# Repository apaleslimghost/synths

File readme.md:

<h1 align="center">
	
</h1>

schematics, PCBs, designs and code for Pale Slim Ghost Synthesisers hardware. these can be viewed on [CADLAB.io](https://cadlab.io/project/26113).

## todo

- [ ] generate build guides with [`pcbdraw populate`](https://github.com/yaqwsx/PcbDraw/blob/master/doc/populate.md)
- [ ] publishing to github pages
- [ ] makefiles with [`kikit`](https://github.com/yaqwsx/KiKit)

## licence

unless otherwise specified:

- hardware is licenced under [CERN-OHL-S](licence-hardware.txt)
- software/firmware is licenced under [Parity Public Licence 7.0.0](licence.md)
- artwork is licenced under [Creative Commons BY-NC-SA 4.0](https://creativecommons.org/licenses/by-nc-sa/4.0/)

generally, that means you can use, edit, and make things in this repository, but please share the source if you do.

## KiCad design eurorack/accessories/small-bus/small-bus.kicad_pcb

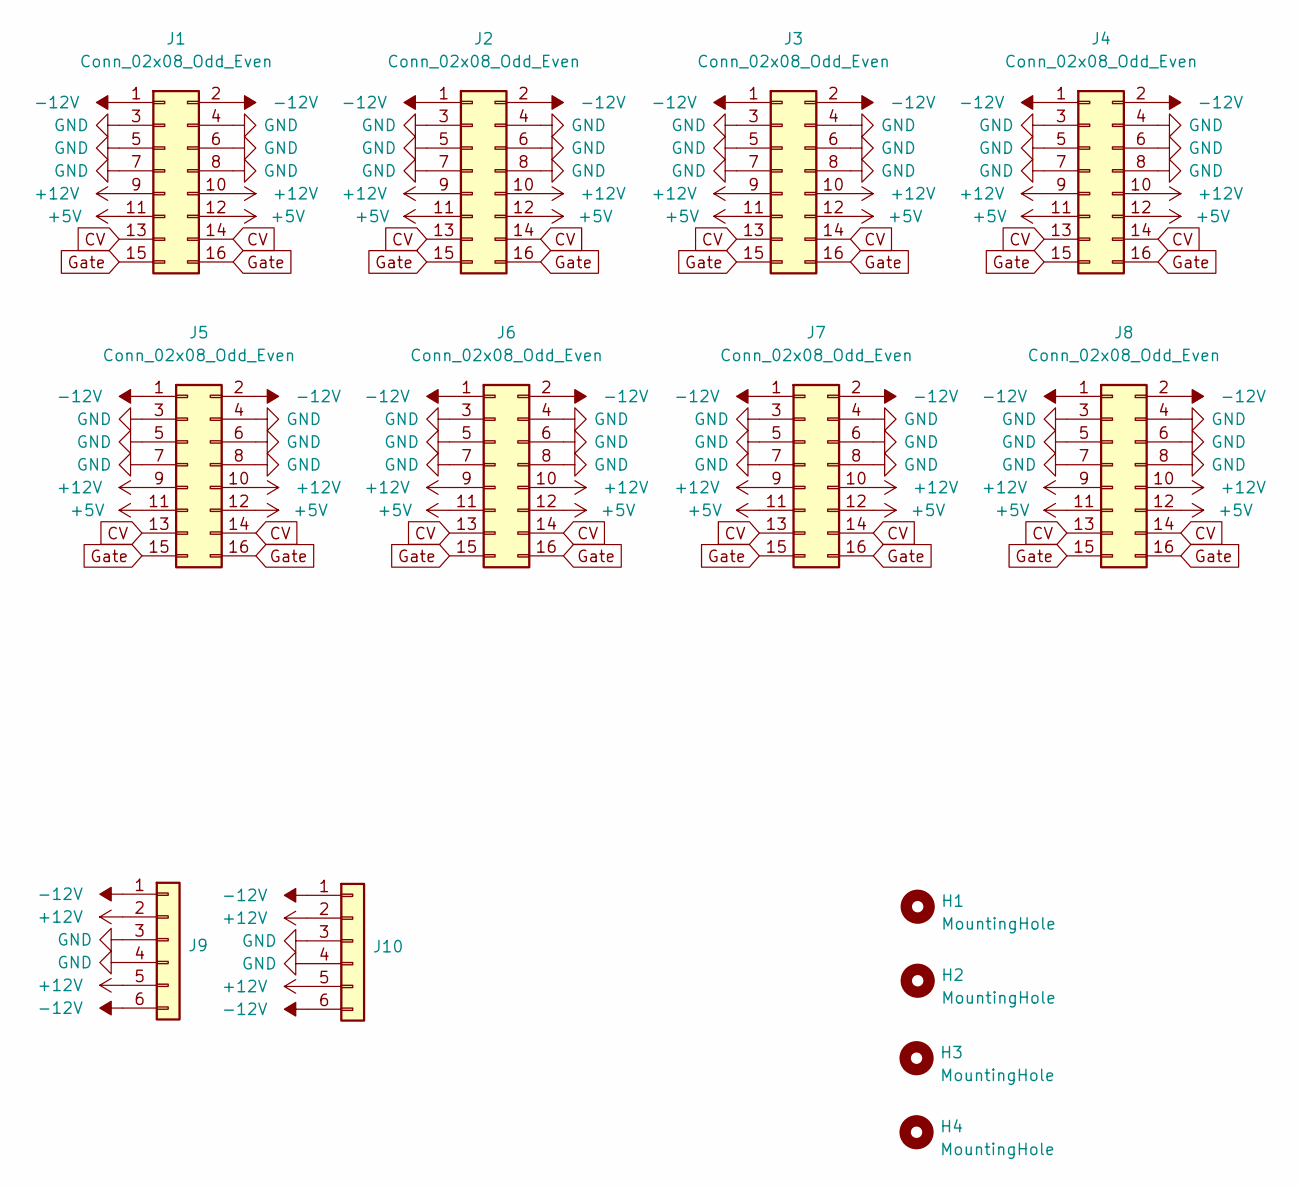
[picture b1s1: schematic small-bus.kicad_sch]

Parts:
H1, H2, H3, H4: MountingHole; MountingHole_3.2mm_M3
J1, J2, J3, J4, J5, J6, J7, J8: Conn_02x08_Odd_Even; PinHeader_2x08_P2.54mm_Edge
J9, J10: Conn_01x06; Molex_KK-254_AE-6410-06A_1x06_P2.54mm_Horizontal

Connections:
+5V: J1.11, J1.12, J2.11, J2.12, J3.11, J3.12, J4.11, J4.12, J5.11, J5.12, J6.11, J6.12, J7.11, J7.12, J8.11, J8.12
+12V: J1.9, J1.10, J2.9, J2.10, J3.9, J3.10, J4.9, J4.10, J5.9, J5.10, J6.9, J6.10, J7.9, J7.10, J8.9, J8.10, J9.2, J9.5, J10.2, J10.5
-12V: J1.1, J1.2, J2.1, J2.2, J3.1, J3.2, J4.1, J4.2, J5.1, J5.2, J6.1, J6.2, J7.1, J7.2, J8.1, J8.2, J9.1, J9.6, J10.1, J10.6
CV: J1.13, J1.14, J2.13, J2.14, J3.13, J3.14, J4.13, J4.14, J5.13, J5.14, J6.13, J6.14, J7.13, J7.14, J8.13, J8.14
GND: J1.3, J1.4, J1.5, J1.6, J1.7, J1.8, J2.3, J2.4, J2.5, J2.6, J2.7, J2.8, J3.3, J3.4, J3.5, J3.6, J3.7, J3.8, J4.3, J4.4, J4.5, J4.6, J4.7, J4.8, J5.3, J5.4, J5.5, J5.6, J5.7, J5.8, J6.3, J6.4, J6.5, J6.6, J6.7, J6.8, J7.3, J7.4, J7.5, J7.6, J7.7, J7.8, J8.3, J8.4, J8.5, J8.6, J8.7, J8.8, J9.3, J9.4, J10.3, J10.4
Gate: J1.15, J1.16, J2.15, J2.16, J3.15, J3.16, J4.15, J4.16, J5.15, J5.16, J6.15, J6.16, J7.15, J7.16, J8.15, J8.16

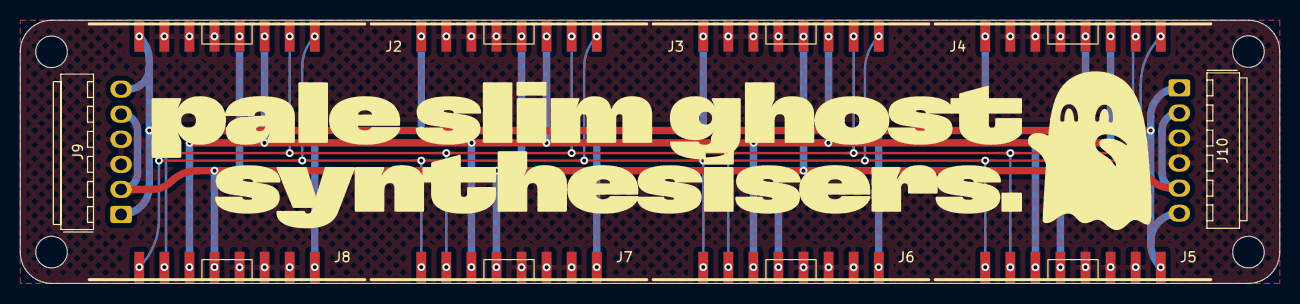
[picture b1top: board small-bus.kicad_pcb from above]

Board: 2 copper layers, 127.6 x 26.7 mm, 14 parts (0 on the bottom side), 6 nets.

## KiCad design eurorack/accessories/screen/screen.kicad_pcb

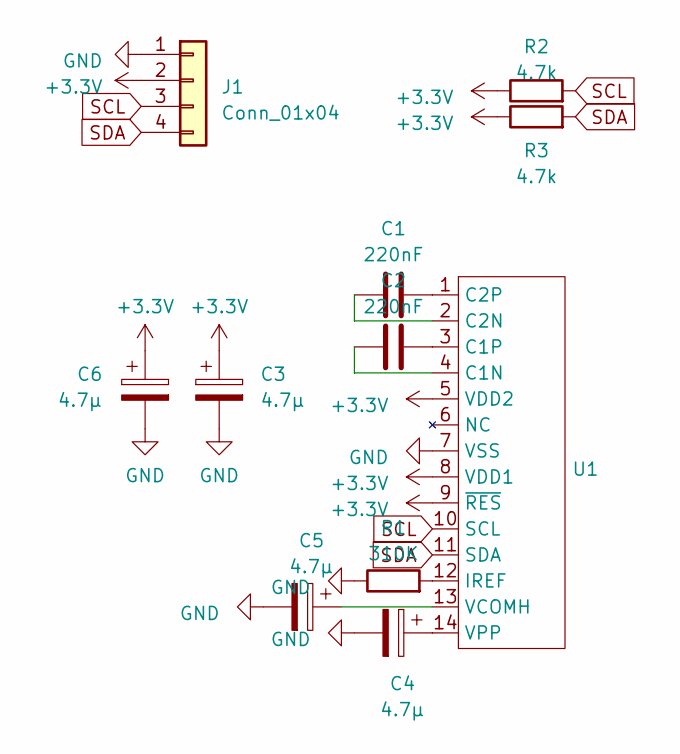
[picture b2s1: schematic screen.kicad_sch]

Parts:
C1, C2: 220nF; C_0402_1005Metric; LCSC C16772
C3, C4, C5, C6: 4.7μ; C_0402_1005Metric; LCSC C23733
J1: Conn_01x04; PinHeader_1x04_P2.54mm_Vertical
R1: 310K; R_0402_1005Metric; LCSC C25104
R2, R3: 4.7k; R_0402_1005Metric; LCSC C25900
U1: ER-OLED0.50-1

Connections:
+3.3V: C3.1, C6.1, J1.2, R2.1, R3.1, U1.5 (VDD2), U1.8 (VDD1), U1.9 (~RES)
GND: C3.2, C4.2, C5.2, C6.2, J1.1, R1.1, U1.7 (VSS)
unnamed: C2.1, U1.4 (C1N)
unnamed: C2.2, U1.3 (C1P)
unnamed: C1.1, U1.2 (C2N)
unnamed: C1.2, U1.1 (C2P)
unnamed: R1.2, U1.12 (IREF)
unnamed: C5.1, U1.13 (VCOMH)
unnamed: C4.1, U1.14 (VPP)
SCL: J1.3, R2.2, U1.10 (SCL)
SDA: J1.4, R3.2, U1.11 (SDA)

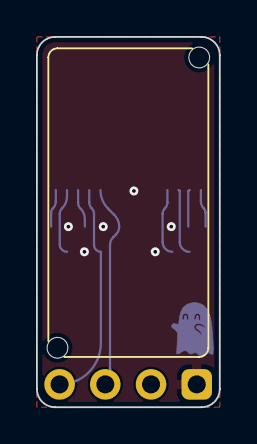
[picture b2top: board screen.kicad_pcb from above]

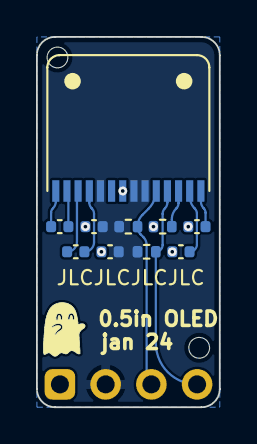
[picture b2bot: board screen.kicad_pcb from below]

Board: 2 copper layers, 10.2 x 20.6 mm, 13 parts (11 on the bottom side), 11 nets.

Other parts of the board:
H1, H2: hole JLCPCB tooling

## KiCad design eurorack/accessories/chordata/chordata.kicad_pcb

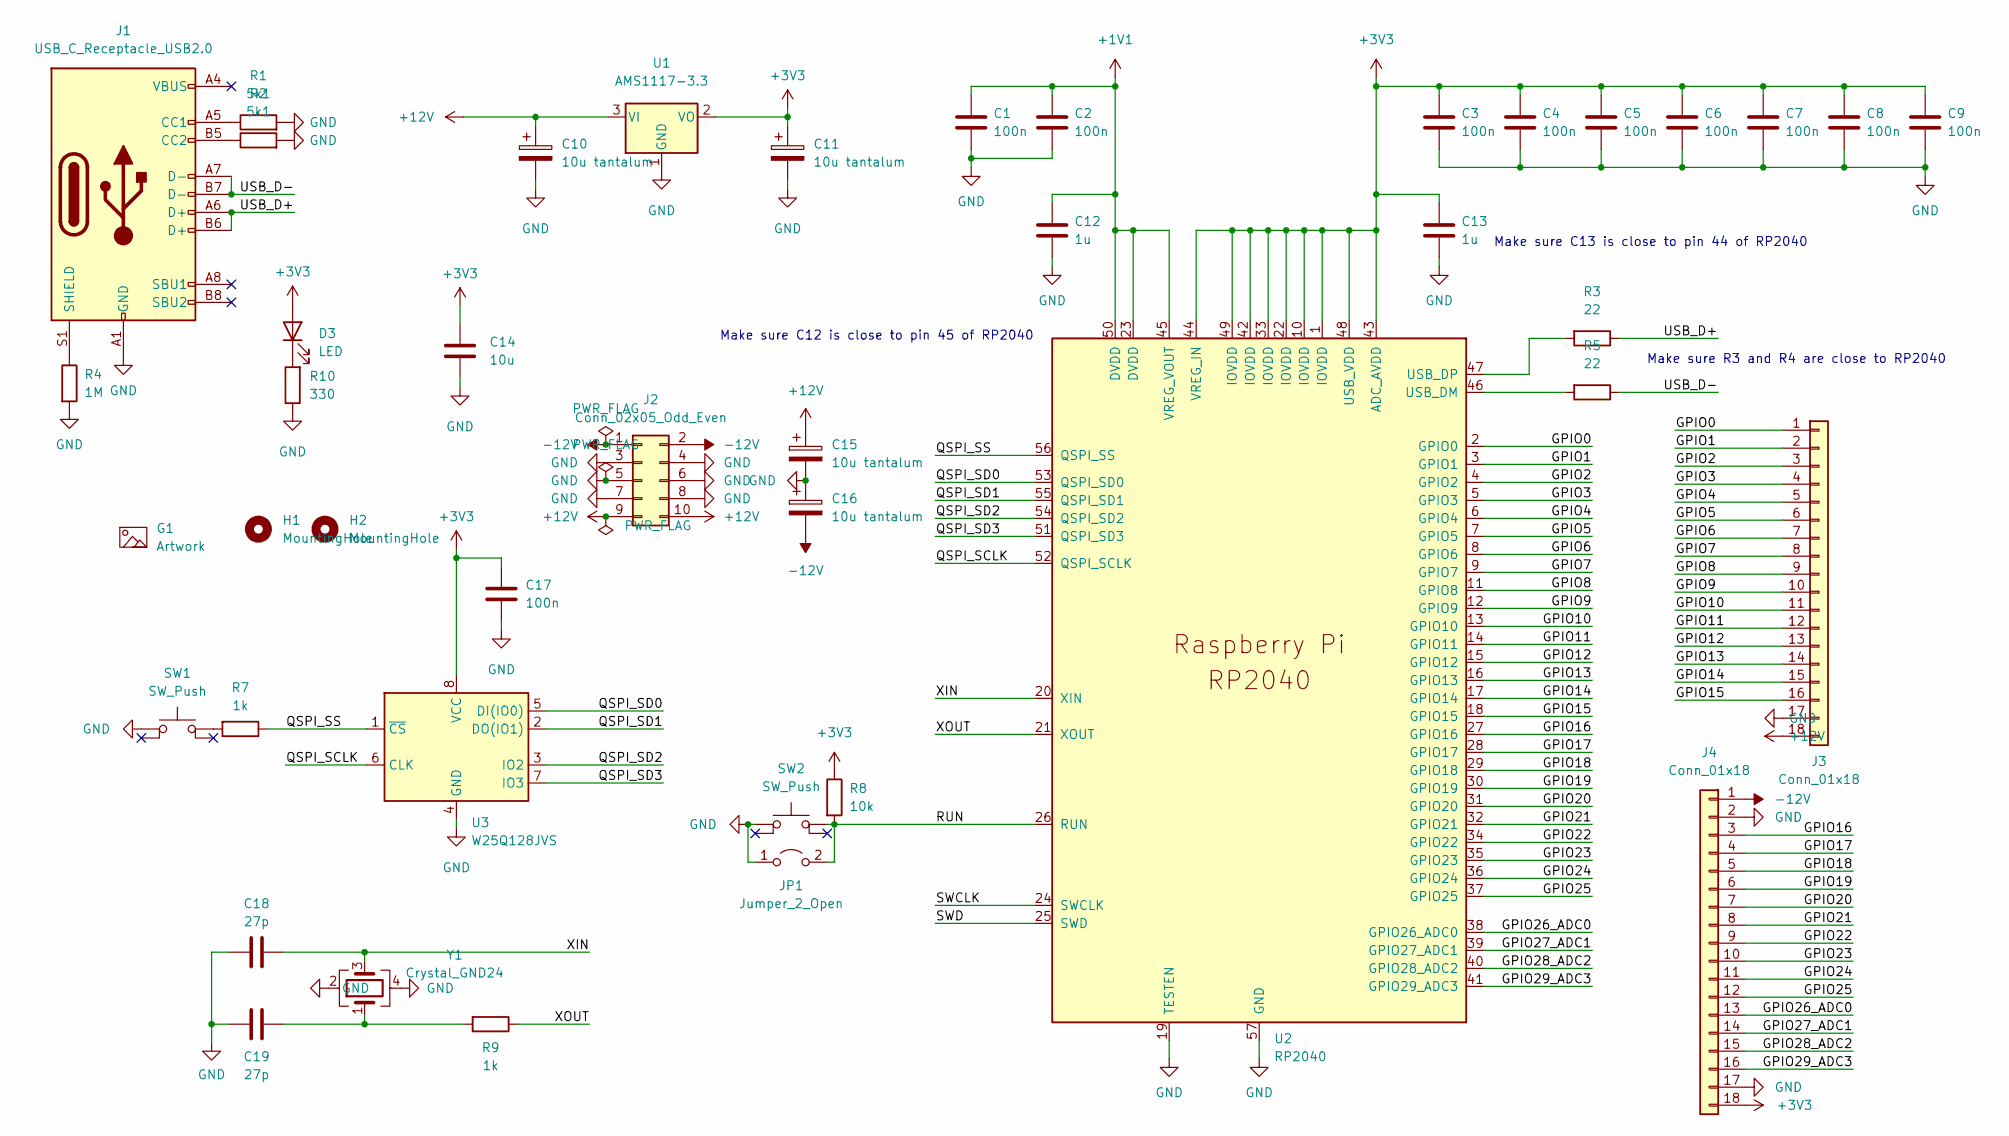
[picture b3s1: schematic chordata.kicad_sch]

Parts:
C1, C2, C3, C4, C5, C6, C7, C8, C9, C17: 100n; C_0402_1005Metric
C10, C11, C15, C16: 10u tantalum; CP_EIA-3216-18_Kemet-A
C12, C13: 1u; C_0402_1005Metric
C14: 10u; C_0805_2012Metric
C18, C19: 27p; C_0402_1005Metric
D3: LED; LED_0603_1608Metric
G1: Artwork; logo 12mm
H1, H2: MountingHole; hole JLCPCB tooling
J1: USB_C_Receptacle_USB2.0; USB_C_Receptacle_GCT_USB4085
J2: Conn_02x05_Odd_Even; PinHeader_Shrouded_2x05_P2.54mm_Horizontal
J3, J4: Conn_01x18; PinHeader_1x18_P2.54mm_Vertical
JP1: Jumper_2_Open; SolderJumper-2_P1.3mm_Open_Pad1.0x1.5mm
R1, R2: 5k1; R_0402_1005Metric
R3, R5: 22; R_0402_1005Metric
R4: 1M; R_0402_1005Metric
R7, R9: 1k; R_0402_1005Metric
R8: 10k; R_0402_1005Metric
R10: 330; R_0402_1005Metric
SW1, SW2: SW_Push; SW_Push_1P1T_NO_CK_KMR2
U1: AMS1117-3.3; SOT-223-3_TabPin2
U2: RP2040; QFN-56-1EP_7x7mm_P0.4mm_EP3.2x3.2mm_ThermalVias
U3: W25Q128JVS; SOIC-8_5.23x5.23mm_P1.27mm
Y1: Crystal_GND24; Crystal_SMD_3225-4Pin_3.2x2.5mm

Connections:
+1V1: C1.1, C2.1, C12.1, U2.23 (DVDD), U2.45 (VREG_VOUT), U2.50 (DVDD)
+3V3: C3.1, C4.1, C5.1, C6.1, C7.1, C8.1, C9.1, C11.1, C13.1, C14.1, C17.1, D3.2 (A), J4.18, R8.1, U1.2 (VO), U2.1 (IOVDD), U2.10 (IOVDD), U2.22 (IOVDD), U2.33 (IOVDD), U2.42 (IOVDD), U2.43 (ADC_AVDD), U2.44 (VREG_IN), U2.48 (USB_VDD), U2.49 (IOVDD), U3.8 (VCC)
+12V: C10.1, C15.1, J2.9, J2.10, J3.18, U1.3 (VI)
-12V: C16.2, J2.1, J2.2, J4.1
/GPIO0: J3.1, U2.2 (GPIO0)
/GPIO1: J3.2, U2.3 (GPIO1)
/GPIO2: J3.3, U2.4 (GPIO2)
/GPIO3: J3.4, U2.5 (GPIO3)
/GPIO4: J3.5, U2.6 (GPIO4)
/GPIO5: J3.6, U2.7 (GPIO5)
/GPIO6: J3.7, U2.8 (GPIO6)
/GPIO7: J3.8, U2.9 (GPIO7)
/GPIO8: J3.9, U2.11 (GPIO8)
/GPIO9: J3.10, U2.12 (GPIO9)
/GPIO10: J3.11, U2.13 (GPIO10)
/GPIO11: J3.12, U2.14 (GPIO11)
/GPIO12: J3.13, U2.15 (GPIO12)
/GPIO13: J3.14, U2.16 (GPIO13)
/GPIO14: J3.15, U2.17 (GPIO14)
/GPIO15: J3.16, U2.18 (GPIO15)
/GPIO16: J4.3, U2.27 (GPIO16)
/GPIO17: J4.4, U2.28 (GPIO17)
/GPIO18: J4.5, U2.29 (GPIO18)
/GPIO19: J4.6, U2.30 (GPIO19)
/GPIO20: J4.7, U2.31 (GPIO20)
/GPIO21: J4.8, U2.32 (GPIO21)
/GPIO22: J4.9, U2.34 (GPIO22)
/GPIO23: J4.10, U2.35 (GPIO23)
/GPIO24: J4.11, U2.36 (GPIO24)
/GPIO25: J4.12, U2.37 (GPIO25)
/GPIO26_ADC0: J4.13, U2.38 (GPIO26_ADC0)
/GPIO27_ADC1: J4.14, U2.39 (GPIO27_ADC1)
/GPIO28_ADC2: J4.15, U2.40 (GPIO28_ADC2)
/GPIO29_ADC3: J4.16, U2.41 (GPIO29_ADC3)
/QSPI_SCLK: U2.52 (QSPI_SCLK), U3.6 (CLK)
/QSPI_SD0: U2.53 (QSPI_SD0), U3.5 (DI(IO0))
/QSPI_SD1: U2.55 (QSPI_SD1), U3.2 (DO(IO1))
/QSPI_SD2: U2.54 (QSPI_SD2), U3.3 (IO2)
/QSPI_SD3: U2.51 (QSPI_SD3), U3.7 (IO3)
/QSPI_SS: R7.1, U2.56 (QSPI_SS), U3.1 (~CS)
/RUN: JP1.2 (B), R8.2, SW2.2, U2.26 (RUN)
/SWCLK: U2.24 (SWCLK)
/SWD: U2.25 (SWD)
/USB_D+: J1.A6 (D+), J1.B6 (D+), R3.1
/USB_D-: J1.A7 (D-), J1.B7 (D-), R5.1
/XIN: C18.1, U2.20 (XIN), Y1.3
/XOUT: R9.1, U2.21 (XOUT)
GND: C1.2, C2.2, C3.2, C4.2, C5.2, C6.2, C7.2, C8.2, C9.2, C10.2, C11.2, C12.2, C13.2, C14.2, C15.2, C16.1, C17.2, C18.2, C19.2, J1.A1 (GND), J1.A12 (GND), J1.B1 (GND), J1.B12 (GND), J2.3, J2.4, J2.5, J2.6, J2.7, J2.8, J3.17, J4.2, J4.17, JP1.1 (A), R1.2, R2.2, R4.2, R10.1, SW1.1, SW2.1, U1.1 (GND), U2.19 (TESTEN), U2.57 (GND), U3.4 (GND), Y1.2, Y1.4
unnamed: C19.1, R9.2, Y1.1
unnamed: D3.1 (K), R10.2
unnamed: J1.A5 (CC1), R1.1
unnamed: J1.B5 (CC2), R2.1
unnamed: J1.S1 (SHIELD), R4.1
unnamed: R3.2, U2.47 (USB_DP)
unnamed: R5.2, U2.46 (USB_DM)
unnamed: R7.2, SW1.2

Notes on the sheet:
Make sure C13 is close to pin 44 of RP2040
Make sure C12 is close to pin 45 of RP2040
Make sure R3 and R4 are close to RP2040

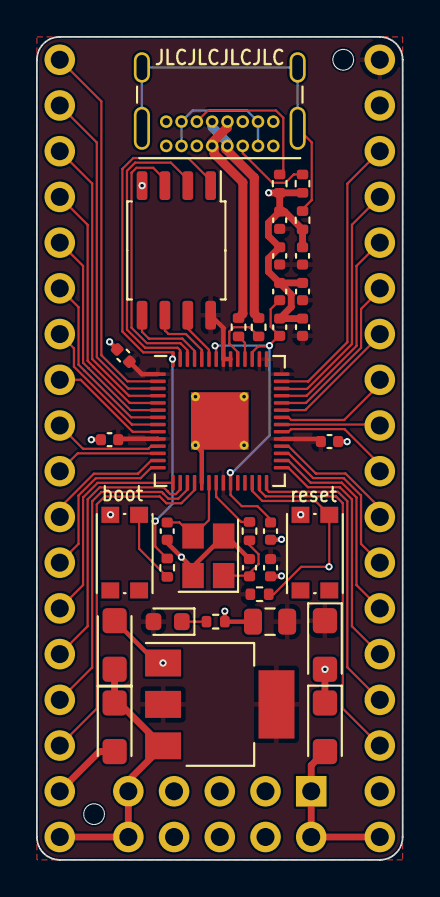
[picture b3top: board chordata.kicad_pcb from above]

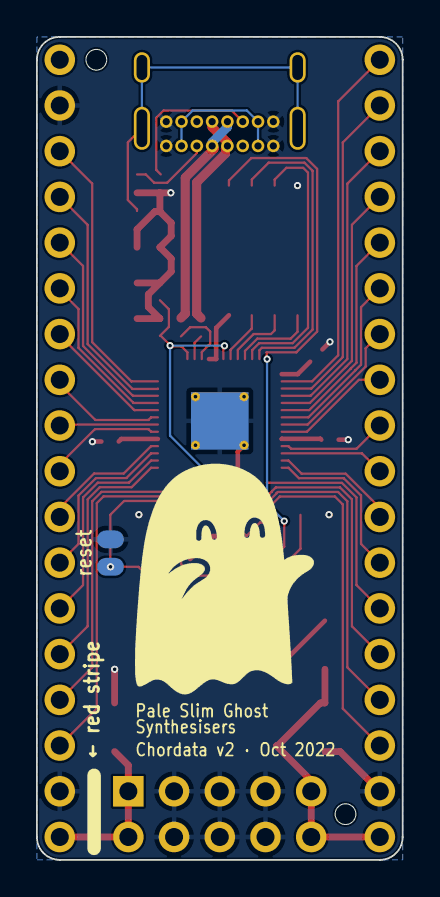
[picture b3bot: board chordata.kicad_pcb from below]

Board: 2 copper layers, 20.3 x 45.7 mm, 43 parts (2 on the bottom side), 54 nets.

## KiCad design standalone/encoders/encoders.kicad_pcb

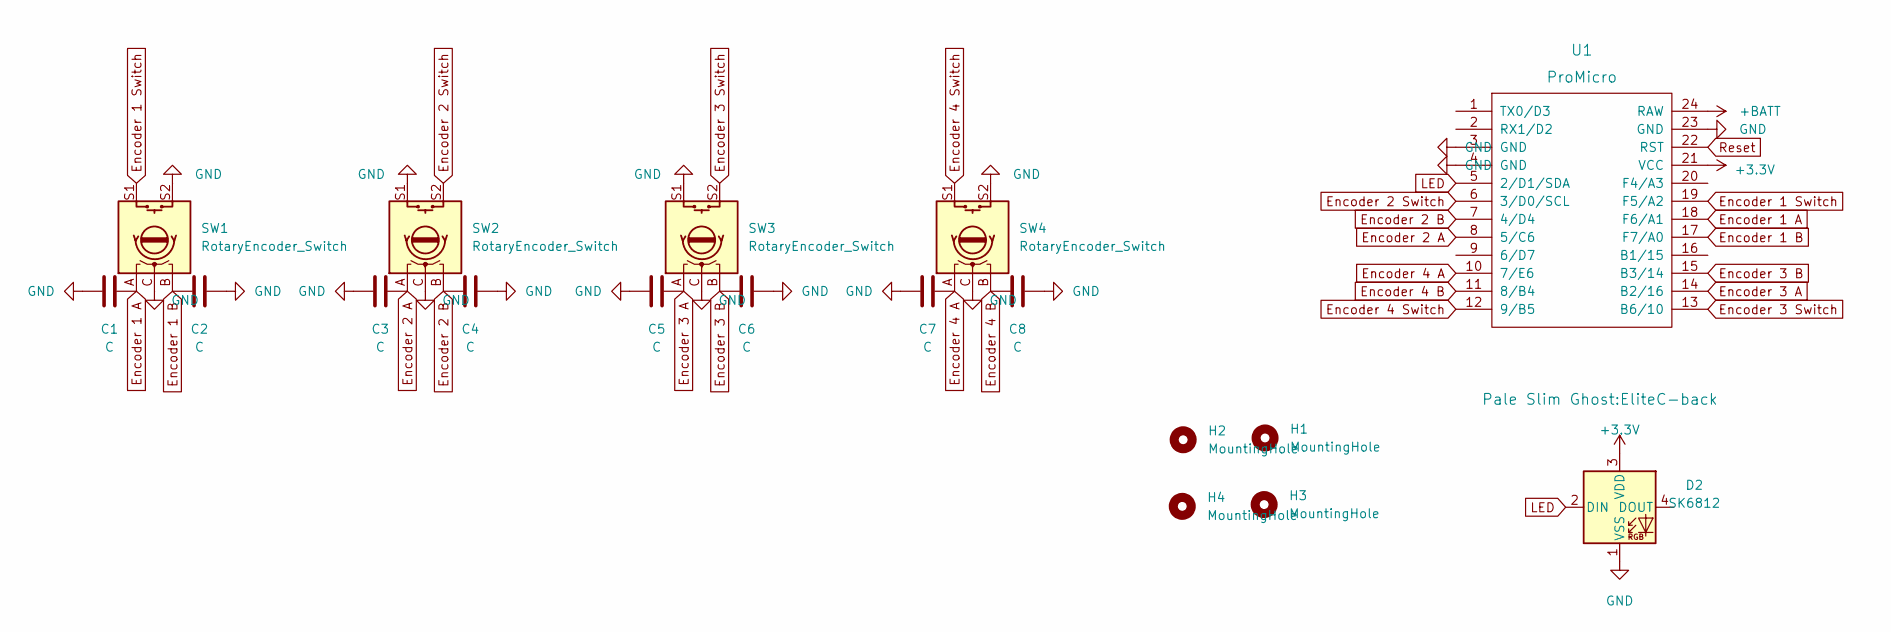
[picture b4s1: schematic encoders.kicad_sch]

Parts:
C1, C2, C3, C4, C5, C6, C7, C8: C; C_0805_2012Metric_Pad1.18x1.45mm_HandSolder
D2: SK6812; LED_SK6812_PLCC4_5.0x5.0mm_P3.2mm
H1, H2, H3, H4: MountingHole; MountingHole_2.2mm_M2_Pad_TopOnly
SW1, SW2, SW3, SW4: RotaryEncoder_Switch; RotaryEncoder_EC11
U1: ProMicro; EliteC-back

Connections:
+3.3V: D2.3 (VDD), U1.21 (VCC)
+BATT: U1.24 (RAW)
Encoder 1 A: C1.2, SW1.A, U1.18 (F6/A1)
Encoder 1 B: C2.1, SW1.B, U1.17 (F7/A0)
Encoder 1 Switch: SW1.S1, U1.19 (F5/A2)
Encoder 2 A: C3.2, SW2.A, U1.8 (5/C6)
Encoder 2 B: C4.1, SW2.B, U1.7 (4/D4)
Encoder 2 Switch: SW2.S2, U1.6 (3/D0/SCL)
Encoder 3 A: C5.2, SW3.A, U1.14 (B2/16)
Encoder 3 B: C6.1, SW3.B, U1.15 (B3/14)
Encoder 3 Switch: SW3.S2, U1.13 (B6/10)
Encoder 4 A: C7.2, SW4.A, U1.10 (7/E6)
Encoder 4 B: C8.1, SW4.B, U1.11 (8/B4)
Encoder 4 Switch: SW4.S1, U1.12 (9/B5)
GND: C1.1, C2.2, C3.1, C4.2, C5.1, C6.2, C7.1, C8.2, D2.1 (VSS), SW1.C, SW1.S2, SW2.C, SW2.S1, SW3.C, SW3.S1, SW4.C, SW4.S2, U1.3 (GND), U1.4 (GND), U1.23 (GND)
LED: D2.2 (DIN), U1.5 (2/D1/SDA)
Reset: U1.22 (RST)

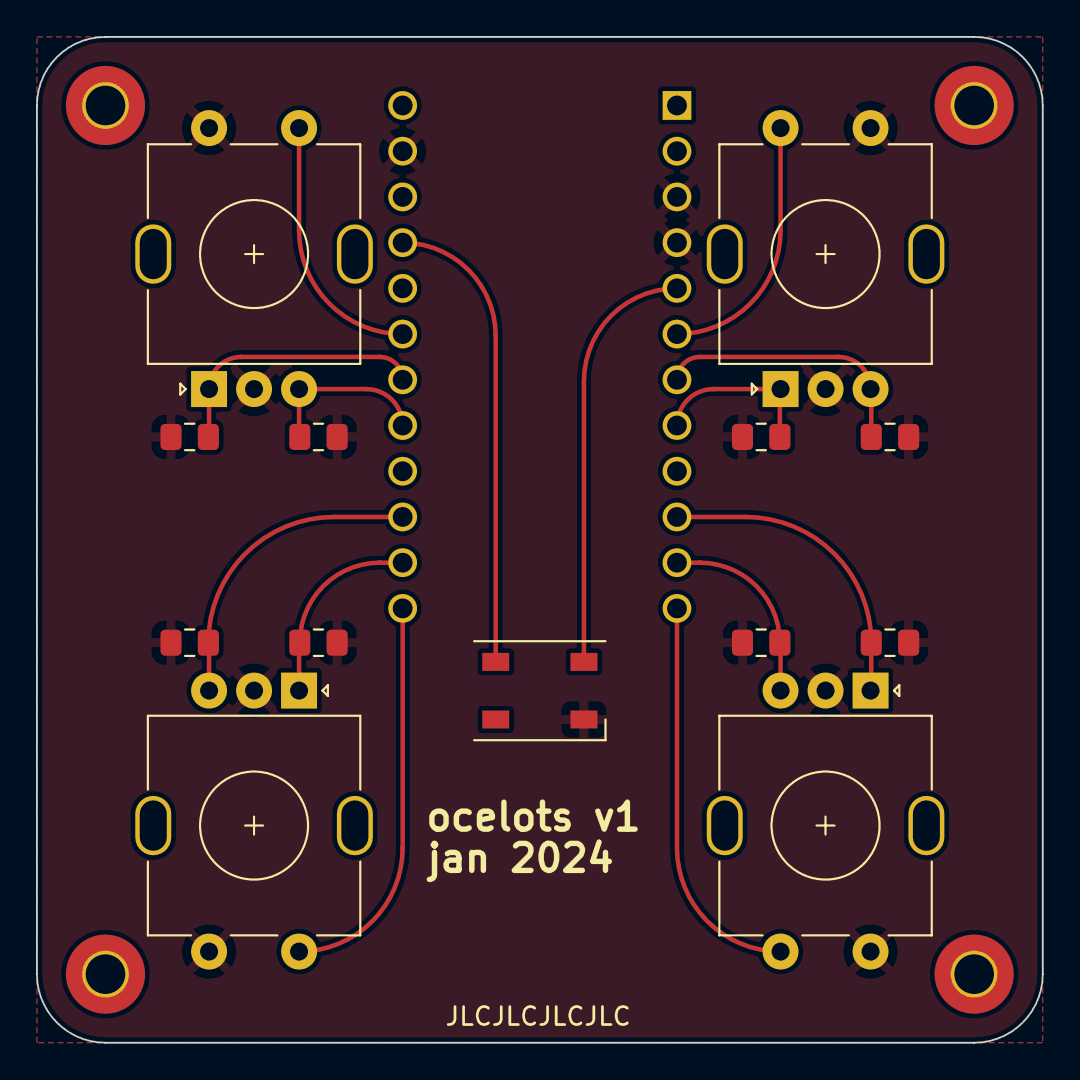
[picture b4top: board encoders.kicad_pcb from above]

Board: 2 copper layers, 55.9 x 55.9 mm, 18 parts (1 on the bottom side), 15 nets.

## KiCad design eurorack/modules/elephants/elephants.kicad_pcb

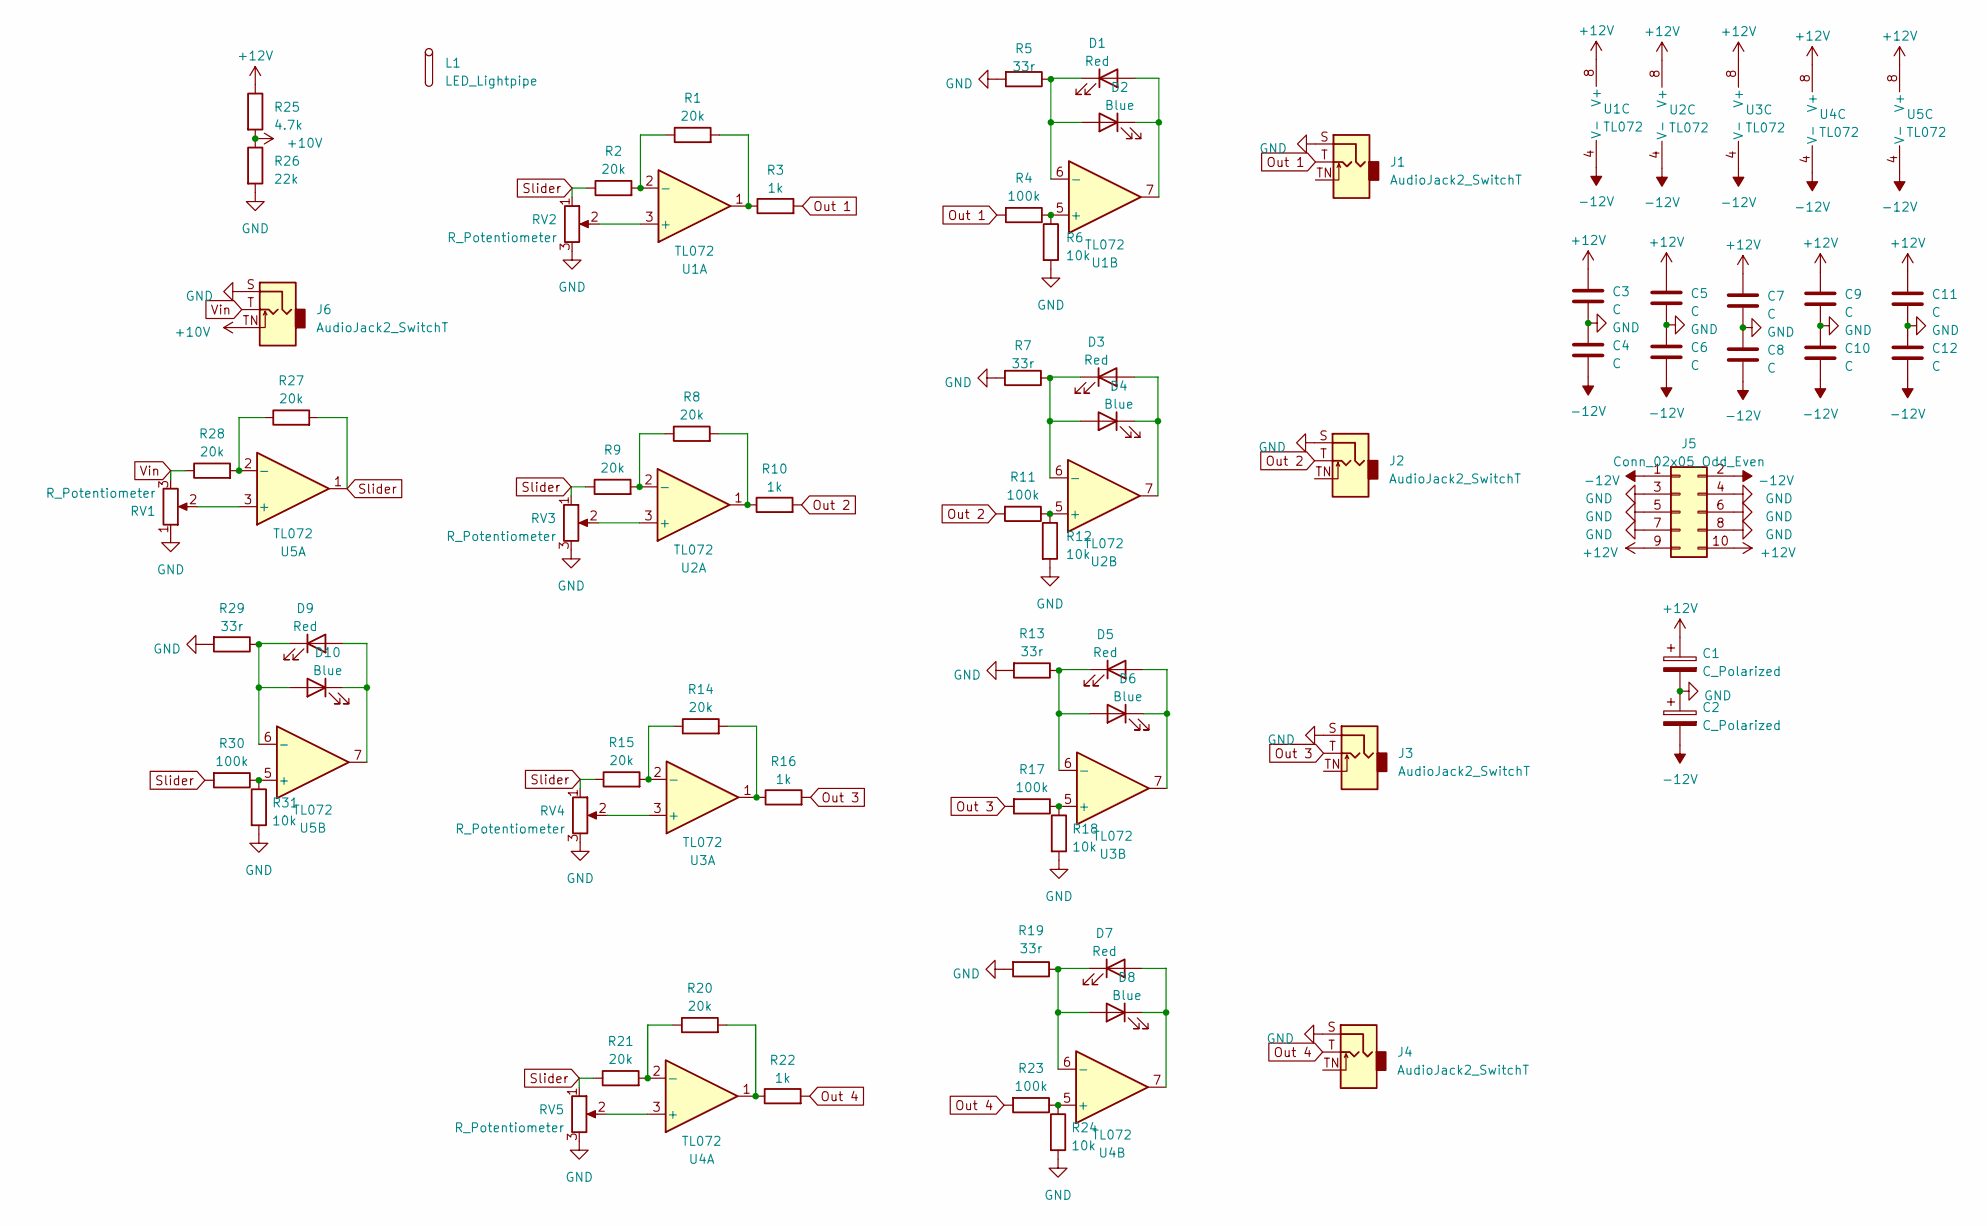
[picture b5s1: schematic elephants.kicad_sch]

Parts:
C1, C2: C_Polarized; CP_EIA-3216-18_Kemet-A; LCSC C7171
C3, C4, C5, C6, C7, C8, C9, C10, C11, C12: C; C_0402_1005Metric; LCSC C1525
D1, D3, D5, D7, D9: Red; LED_0805_2012Metric_Pad1.15x1.40mm_HandSolder
D2, D4, D6, D8, D10: Blue; LED_0805_2012Metric_Pad1.15x1.40mm_HandSolder
J1, J2, J3, J4, J6: AudioJack2_SwitchT; Jack_3.5mm_QingPu_WQP-PJ398SM_Vertical
J5: Conn_02x05_Odd_Even; PinHeader_2x05_P2.54mm_Vertical_SMD
L1: LED_Lightpipe; VBL Lightpipe
R1, R2, R8, R9, R14, R15, R20, R21, R27, R28: 20k; R_0402_1005Metric; LCSC C25765
R3, R10, R16, R22: 1k; R_0402_1005Metric; LCSC C11702
R4, R11, R17, R23, R30: 100k; R_0402_1005Metric; LCSC C25741
R5, R7, R13, R19, R29: 33r; R_0402_1005Metric; LCSC C25105
R6, R12, R18, R24, R31: 10k; R_0402_1005Metric; LCSC C25744
R25: 4.7k; R_0402_1005Metric; LCSC C25900
R26: 22k; R_0402_1005Metric; LCSC C25768
RV1: R_Potentiometer; Potentiometer_Alpha_RD901F-40-00D_Single_Vertical
RV2, RV3, RV4, RV5: R_Potentiometer; Potentiometer_Song_Huei_R0904N
U1, U2, U3, U4, U5: TL072; SOT-23-8; LCSC C4370550

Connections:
+10V: J6.TN, R25.2, R26.1
+12V: C1.1, C3.1, C5.1, C7.1, C9.1, C11.1, J5.9, J5.10, R25.1, U1.8 (V+), U2.8 (V+), U3.8 (V+), U4.8 (V+), U5.8 (V+)
-12V: C2.2, C4.2, C6.2, C8.2, C10.2, C12.2, J5.1, J5.2, U1.4 (V-), U2.4 (V-), U3.4 (V-), U4.4 (V-), U5.4 (V-)
GND: C1.2, C2.1, C3.2, C4.1, C5.2, C6.1, C7.2, C8.1, C9.2, C10.1, C11.2, C12.1, J1.S, J2.S, J3.S, J4.S, J5.3, J5.4, J5.5, J5.6, J5.7, J5.8, J6.S, R5.2, R6.2, R7.2, R12.2, R13.2, R18.2, R19.2, R24.2, R26.2, R29.2, R31.2, RV1.1, RV2.3, RV3.3, RV4.3, RV5.3
unnamed: D1.2 (A), D2.1 (K), U1.7
unnamed: D1.1 (K), D2.2 (A), R5.1, U1.6 (-)
unnamed: D3.2 (A), D4.1 (K), U2.7
unnamed: D3.1 (K), D4.2 (A), R7.1, U2.6 (-)
unnamed: D5.2 (A), D6.1 (K), U3.7
unnamed: D5.1 (K), D6.2 (A), R13.1, U3.6 (-)
unnamed: D7.2 (A), D8.1 (K), U4.7
unnamed: D7.1 (K), D8.2 (A), R19.1, U4.6 (-)
unnamed: D9.1 (K), D10.2 (A), R29.1, U5.6 (-)
unnamed: D9.2 (A), D10.1 (K), U5.7
unnamed: R1.2, R3.1, U1.1
unnamed: R8.2, R10.1, U2.1
unnamed: R14.2, R16.1, U3.1
unnamed: R20.2, R22.1, U4.1
unnamed: RV2.2, U1.3 (+)
unnamed: R1.1, R2.2, U1.2 (-)
unnamed: R4.1, R6.1, U1.5 (+)
unnamed: RV3.2, U2.3 (+)
unnamed: R8.1, R9.2, U2.2 (-)
unnamed: R11.1, R12.1, U2.5 (+)
unnamed: RV4.2, U3.3 (+)
unnamed: R14.1, R15.2, U3.2 (-)
unnamed: R17.1, R18.1, U3.5 (+)
unnamed: RV5.2, U4.3 (+)
unnamed: R20.1, R21.2, U4.2 (-)
unnamed: R23.1, R24.1, U4.5 (+)
unnamed: RV1.2, U5.3 (+)
unnamed: R27.1, R28.2, U5.2 (-)
unnamed: R30.1, R31.1, U5.5 (+)
Out 1: J1.T, R3.2, R4.2
Out 2: J2.T, R10.2, R11.2
Out 3: J3.T, R16.2, R17.2
Out 4: J4.T, R22.2, R23.2
Slider: R2.1, R9.1, R15.1, R21.1, R27.2, R30.2, RV2.1, RV3.1, RV4.1, RV5.1, U5.1
Vin: J6.T, R28.1, RV1.3

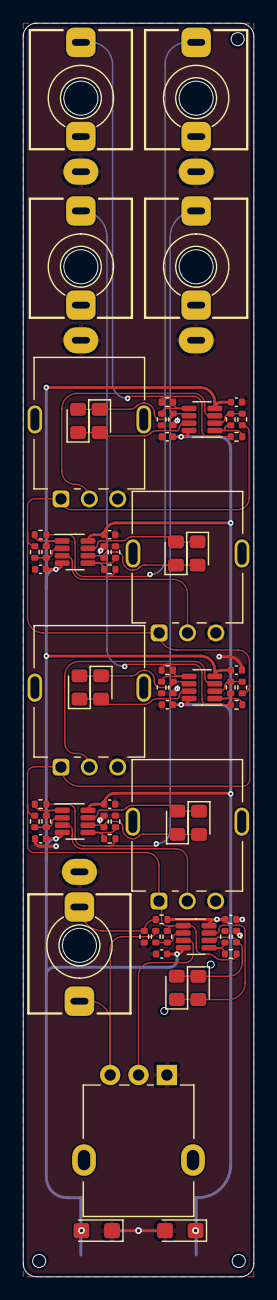
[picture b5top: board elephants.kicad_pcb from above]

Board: 2 copper layers, 20.3 x 110.5 mm, 70 parts (1 on the bottom side), 39 nets.

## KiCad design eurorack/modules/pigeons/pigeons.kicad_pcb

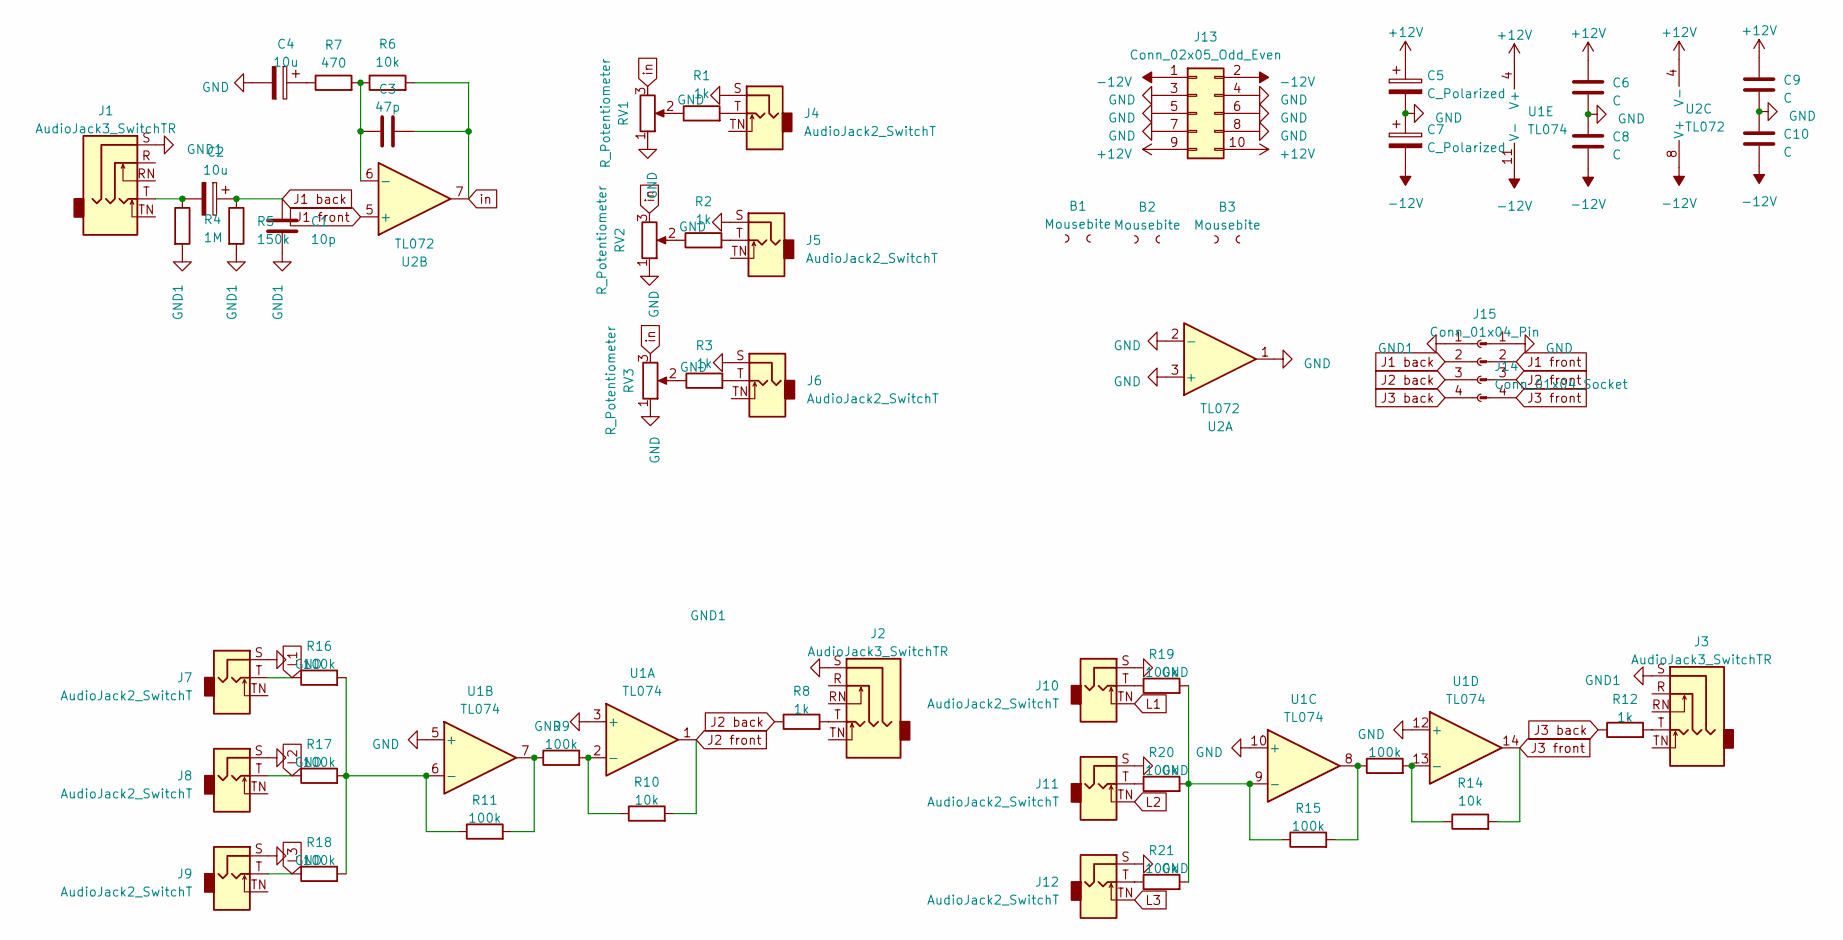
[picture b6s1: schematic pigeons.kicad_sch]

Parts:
B1, B2, B3: Mousebite; mousebite-2.54x5.08mm
C1: 10p; C_0805_2012Metric_Pad1.18x1.45mm_HandSolder
C2, C4: 10u; CP_EIA-3216-18_Kemet-A_Pad1.58x1.35mm_HandSolder
C3: 47p; C_0805_2012Metric_Pad1.18x1.45mm_HandSolder
C5, C7: C_Polarized; CP_EIA-3216-18_Kemet-A_Pad1.58x1.35mm_HandSolder
C6, C8, C9, C10: C; C_0805_2012Metric_Pad1.18x1.45mm_HandSolder
J1, J2, J3: AudioJack3_SwitchTR; Qingpu WQP-PJ612A
J4, J5, J6, J7, J8, J9, J10, J11, J12: AudioJack2_SwitchT; Jack_3.5mm_QingPu_WQP-PJ398SM_Vertical
J13: Conn_02x05_Odd_Even; PinHeader_2x05_P2.54mm_Vertical_SMD
J14: Conn_01x04_Socket; PinSocket_1x04_P2.54mm_Vertical
J15: Conn_01x04_Pin; PinHeader_1x04_P2.54mm_Vertical
R1, R2, R3, R8, R12: 1k; R_0805_2012Metric_Pad1.20x1.40mm_HandSolder
R4: 1M; R_0805_2012Metric_Pad1.20x1.40mm_HandSolder
R5: 150k; R_0805_2012Metric_Pad1.20x1.40mm_HandSolder
R6, R10, R14: 10k; R_0805_2012Metric_Pad1.20x1.40mm_HandSolder
R7: 470; R_0805_2012Metric_Pad1.20x1.40mm_HandSolder
R9, R11, R13, R15, R16, R17, R18, R19, R20, R21: 100k; R_0805_2012Metric_Pad1.20x1.40mm_HandSolder
RV1, RV2, RV3: R_Potentiometer; Potentiometer_Alpha_RD901F-40-00D_Single_Vertical
U1: TL074; SOIC-14_3.9x8.7mm_P1.27mm
U2: TL072; SOIC-8_3.9x4.9mm_P1.27mm

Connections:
+12V: C5.1, C6.1, C9.1, J13.9, J13.10, U1.4 (V+), U2.4 (V-)
-12V: C7.2, C8.2, C10.2, J13.1, J13.2, U1.11 (V-), U2.8 (V+)
GND: C4.2, C5.2, C6.2, C7.1, C8.1, C9.2, C10.1, J4.S, J5.S, J6.S, J7.S, J8.S, J9.S, J10.S, J11.S, J12.S, J13.3, J13.4, J13.5, J13.6, J13.7, J13.8, J15.1, RV1.1, RV2.1, RV3.1, U1.3 (+), U1.5 (+), U1.10 (+), U1.12 (+), U2.1, U2.2 (-), U2.3 (+)
GND1: C1.2, J1.S, J2.S, J3.S, J14.1, R4.2, R5.2
J1 back: C1.1, C2.1, J14.2, R5.1
J1 front: J15.2, U2.5 (+)
J2 back: J14.3, R8.1
J2 front: J15.3, R10.2, U1.1
J3 back: J14.4, R12.1
J3 front: J15.4, R14.2, U1.14
L1: J7.T, J10.TN, R16.1
L2: J8.T, J11.TN, R17.1
L3: J9.T, J12.TN, R18.1
unnamed: C2.2, J1.T, R4.1
unnamed: C4.1, R7.1
unnamed: J2.T, R8.2
unnamed: J3.T, R12.2
unnamed: J4.T, R1.2
unnamed: J5.T, R2.2
unnamed: J6.T, R3.2
unnamed: J10.T, R19.1
unnamed: J11.T, R20.1
unnamed: J12.T, R21.1
unnamed: R1.1, RV1.2
unnamed: R2.1, RV2.2
unnamed: R3.1, RV3.2
unnamed: R9.1, R11.2, U1.7
unnamed: R13.1, R15.2, U1.8
unnamed: R9.2, R10.1, U1.2 (-)
unnamed: R11.1, R16.2, R17.2, R18.2, U1.6 (-)
unnamed: R15.1, R19.2, R20.2, R21.2, U1.9 (-)
unnamed: R13.2, R14.1, U1.13 (-)
unnamed: C3.1, R6.1, R7.2, U2.6 (-)
in: C3.2, R6.2, RV1.3, RV2.3, RV3.3, U2.7

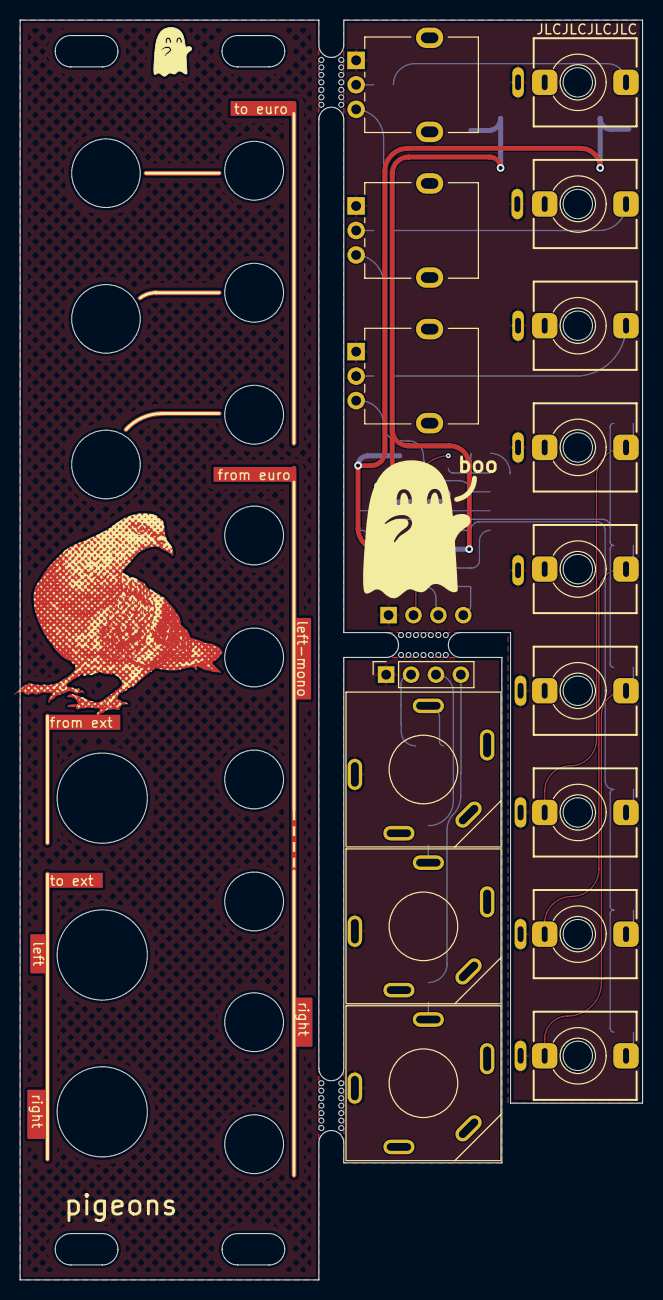
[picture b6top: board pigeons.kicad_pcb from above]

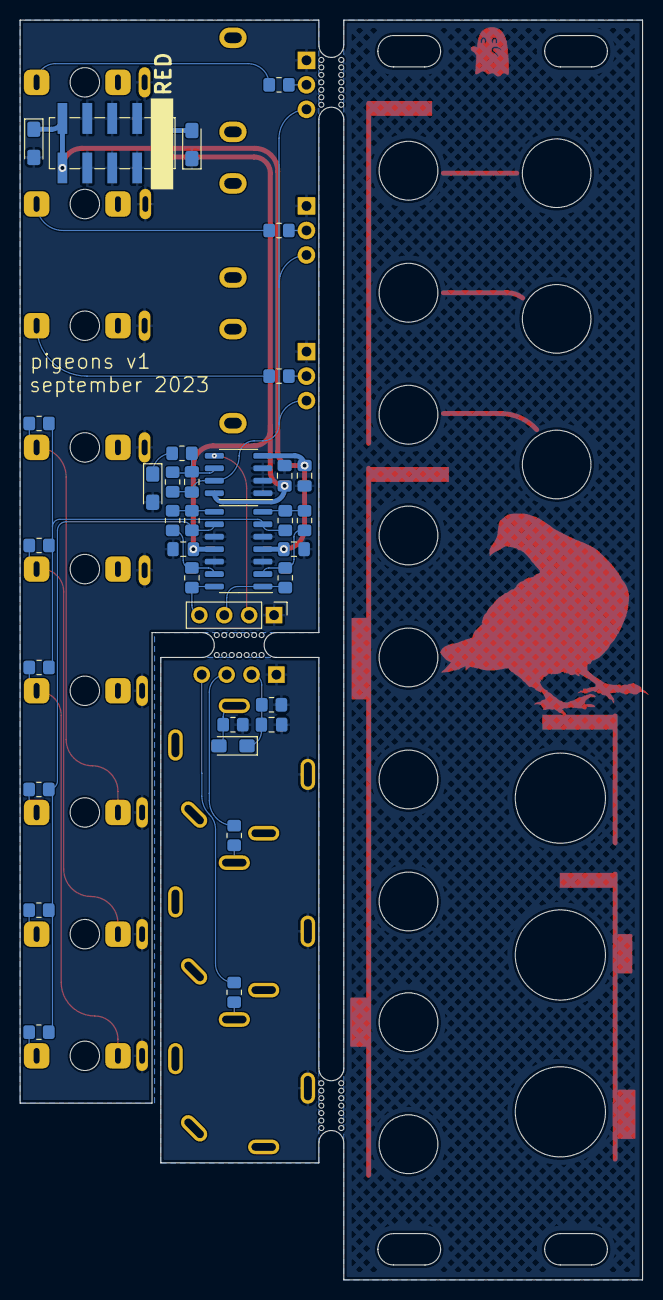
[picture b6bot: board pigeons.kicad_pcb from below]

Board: 2 copper layers, 63.5 x 128.5 mm, 54 parts (35 on the bottom side), 34 nets.

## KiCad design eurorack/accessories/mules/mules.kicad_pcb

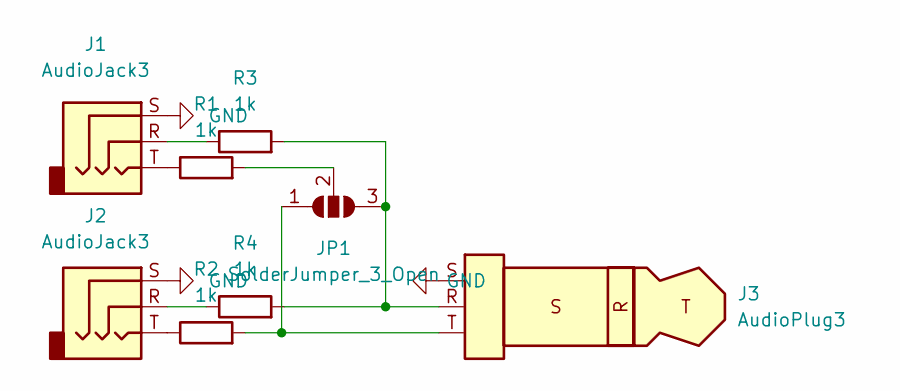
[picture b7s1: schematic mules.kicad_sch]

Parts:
J1, J2: AudioJack3; Jack_3.5mm_CUI_SJ-3523-SMT_Horizontal
J3: AudioPlug3; Plug_3.5mm_CUI_SP-3533
JP1: SolderJumper_3_Open; SolderJumper-3_P1.3mm_Open_RoundedPad1.0x1.5mm
R1, R2, R3, R4: 1k; R_0805_2012Metric_Pad1.20x1.40mm_HandSolder

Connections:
GND: J1.S, J2.S, J3.S
unnamed: J1.R, R3.1
unnamed: J1.T, R1.1
unnamed: J2.R, R4.1
unnamed: J2.T, R2.1
unnamed: J3.R, JP1.3 (B), R3.2, R4.2
unnamed: J3.T, JP1.1 (A), R2.2
unnamed: JP1.2 (C), R1.2

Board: 2 copper layers, 8 parts (0 on the bottom side), 8 nets, no tracks yet.
